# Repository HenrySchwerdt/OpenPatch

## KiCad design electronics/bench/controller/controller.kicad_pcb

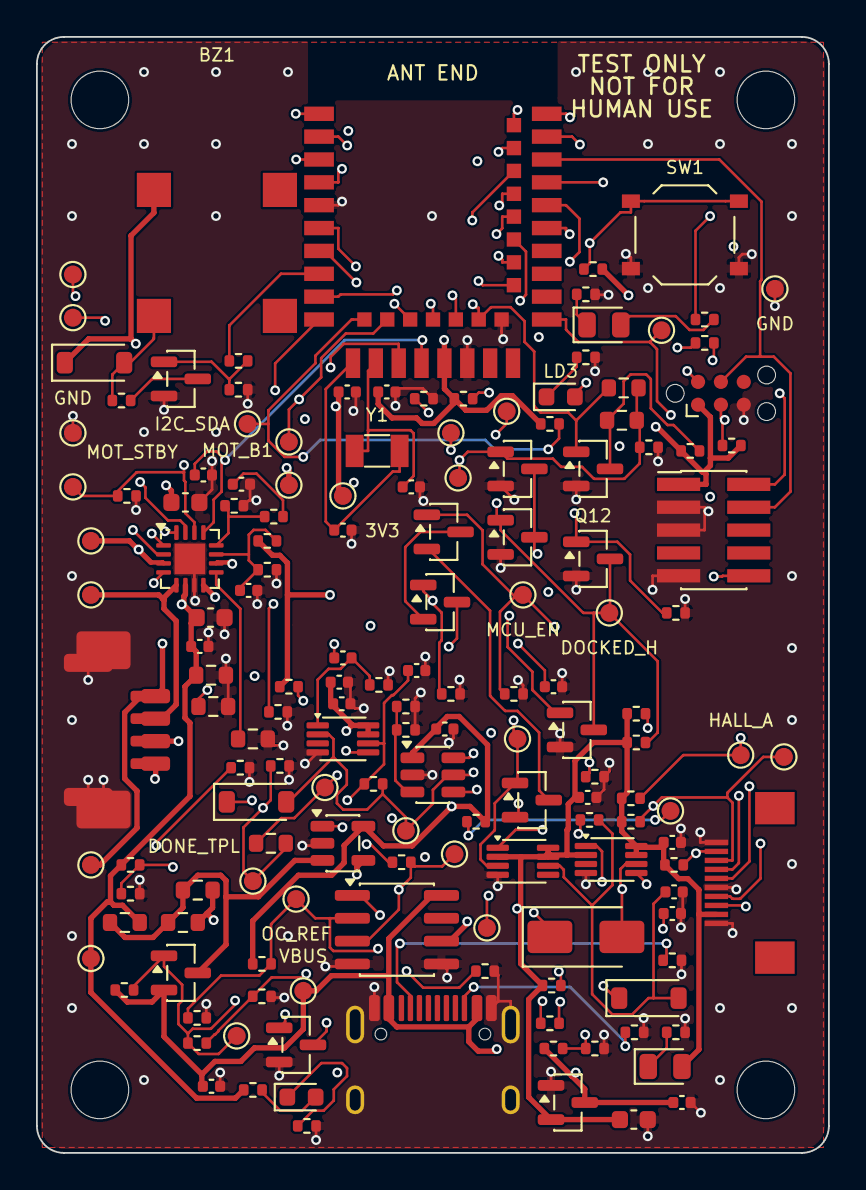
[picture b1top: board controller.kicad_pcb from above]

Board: 4 copper layers, 44.0 x 62.0 mm, 160 parts (0 on the bottom side), 76 nets.

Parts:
BZ1: MLT-8530; Buzzer_MLT-8530_8.5x8.5
C1: 1uF; C_0402_1005Metric
C2: 10uF; C_0603_1608Metric
C4, C20, C24, C25, C26, C27, C28, C29, C33, C34, C35, C36: 100nF; C_0402_1005Metric
C5: 4.7uF; C_0402_1005Metric
C6, C7: 15pF; C_0402_1005Metric
C21, C30, C31, C32: 10nF; C_0402_1005Metric
C22, C23: 10uF 25V; C_0603_1608Metric
D1, D4, D5: 1N4148W; D_SOD-123
D2: SS14; D_SMA
H1, H2, H3, H4: M3; MountingHole_3.2mm_M3
J1: TYPE-C-31-M-12 (power only); USB_C_Receptacle_HRO_TYPE-C-31-M-12
J2: TC2030-IDC-NL; Tag-Connect_TC2030-IDC-NL_2x03_P1.27mm_Vertical
J3: SWD 2x5 1.27 mm; PinHeader_2x05_P1.27mm_Vertical_SMD
J4: FH12-10S-0.5SH(55); Hirose_FH12-10S-0.5SH_1x10-1MP_P0.50mm_Horizontal
J5: PicoBlade 4P (A1251WR-S-4P); Molex_PicoBlade_53261-0471_1x04-1MP_P1.25mm_Horizontal
J6: JST GH SM04B-GHS-TB (DNP alt.); JST_GH_SM04B-GHS-TB_1x04-1MP_P1.25mm_Horizontal
LD1: green 3V3; LED_0805_2012Metric
LD2: green status; LED_0805_2012Metric
LD3: red alarm; LED_0603_1608Metric
LD4: red VMOT on; LED_0603_1608Metric
Q4: AO3401A; SOT-23
Q5, Q6, Q7, Q8, Q9, Q10, Q11, Q12, Q13, Q14: 2N7002; SOT-23
R1, R2, R24: 5.1k; R_0402_1005Metric
R3, R6, R7, R9, R11, R38: 100R; R_0402_1005Metric
R4, R5, R12, R23, R25, R33, R34, R35, R36, R40, R41, R42, R43, R46, R52, R53, R98, R99, R100, R103, R106, R109, R111, R112, R113, R116, R117, R118: 100k; R_0402_1005Metric
R8, R32, R37, R102, R104, R110: 1k; R_0402_1005Metric
R10: 22R; R_0402_1005Metric
R20, R21, R31, R39, R47: 1.0R; R_0603_1608Metric
R22, R30: 47k; R_0402_1005Metric
R26, R44, R107, R108, R114, R115: 10k; R_0402_1005Metric
R45: 22k; R_0402_1005Metric
R50, R51, R105: 4.7k; R_0402_1005Metric
R96, R97, R119: 0R; R_0603_1608Metric
R101: 470R; R_0603_1608Metric
SW1: TS-1187A-B-A-B; SW_Push_1P1T_XKB_TS-1187A
TP1, TP27: GND; TestPoint_Pad_D1.0mm
TP2: 3V3; TestPoint_Pad_D1.0mm
TP3: VBUS; TestPoint_Pad_D1.0mm
TP4: VMOT; TestPoint_Pad_D1.0mm
TP5: PGATE; TestPoint_Pad_D1.0mm
TP6: LATCH_Q; TestPoint_Pad_D1.0mm
TP7: MCU_EN; TestPoint_Pad_D1.0mm
TP8: DOCKED_H; TestPoint_Pad_D1.0mm
TP9: DOCK_N; TestPoint_Pad_D1.0mm
TP10: LATCH_CLR_N; TestPoint_Pad_D1.0mm
TP11: ARM_CLK; TestPoint_Pad_D1.0mm
TP12: WDT_WAKE; TestPoint_Pad_D1.0mm
TP13: WDT_DONE; TestPoint_Pad_D1.0mm
TP14: NRST; TestPoint_Pad_D1.0mm
TP15: MOT_A1; TestPoint_Pad_D1.0mm
TP16: MOT_A2; TestPoint_Pad_D1.0mm
TP17: MOT_B1; TestPoint_Pad_D1.0mm
TP18: MOT_B2; TestPoint_Pad_D1.0mm
TP19: MOT_STCK; TestPoint_Pad_D1.0mm
TP20: MOT_DIR; TestPoint_Pad_D1.0mm
TP21: MOT_STBY; TestPoint_Pad_D1.0mm
TP22: I_SENSE; TestPoint_Pad_D1.0mm
TP23: HALL_A; TestPoint_Pad_D1.0mm
TP24: HALL_B; TestPoint_Pad_D1.0mm
TP28: I2C_SDA; TestPoint_Pad_D1.0mm
TP29: I2C_SCL; TestPoint_Pad_D1.0mm
TP30: DONE_TPL; TestPoint_Pad_D1.0mm
TP31: OC_OK; TestPoint_Pad_D1.0mm
TP32: OC_REF; TestPoint_Pad_D1.0mm
TP41: DIR_REV; TestPoint_Pad_D1.0mm
U1: E73-2G4M08S1CX; Ebyte_E73-2G4M08S1C_13x18
U2: XC6206P332MR-G; SOT-23
U4: STSPIN220; QFN-16-1EP_3x3mm_P0.5mm_EP1.7x1.7mm
U5: TPL5010DDCR; SOT-23-6
U6: SN74AUP1G74DCUR; VSSOP-8_2.3x2mm_P0.5mm
U7: INA180A1IDBVR; SOT-23-5
U8: LM393DR2G; SOIC-8_3.9x4.9mm_P1.27mm
U9: SN74AUP1G74DCUR (OC latch); VSSOP-8_2.3x2mm_P0.5mm
U10: SN74AUP1G74DCUR (DONE qualifier); VSSOP-8_2.3x2mm_P0.5mm
Y1: 32.768kHz 12.5pF; Crystal_SMD_3215-2Pin_3.2x1.5mm

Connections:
3V3: BZ1.1, C2.1, C4.1, C5.1, C25.1, C27.1, C28.1, C33.1, C36.1, D1.1, J2.1, J3.1, J4.2, LD1.2, R4.2, R5.2, R23.1, R26.1, R40.1, R41.1, R46.2, R50.1, R51.1, R52.1, R53.1, R98.1, R107.1, R108.1, R116.1, TP2.1, U1.19, U2.2, U5.1, U6.2, U6.7, U6.8, U7.5, U8.6, U9.2, U9.7, U9.8, U10.7, U10.8
ARM_CLK: R103.1, TP11.1, U1.32, U6.1
BTN_N: R5.1, SW1.1, U1.28
BUZ_PWM: R11.1, U1.8
BZ_D: Q9.3, R10.2
BZ_G: Q9.1, R11.2, R12.1
BZ_N: BZ1.2, D1.2, R10.1
CC1: J1.A5, R1.1
CC2: J1.B5, R2.1
DIR_INV: Q11.3, R97.1, R98.2
DIR_REV: Q10.1, R96.2, R97.2, R99.1, TP41.1, U1.9
DOCKED_H: Q6.1, Q7.3, Q12.3, R40.2, TP8.1, U1.10
DOCK_N: J4.6, Q7.1, R41.2, TP9.1, U1.3
DOCK_TEST: Q12.1, R117.1, U1.2
DONE_PULSE: C31.2, R104.1, U10.1
DONE_TPL: R118.1, R119.2, TP30.1, U5.4, U10.5
GND: C1.2, C2.2, C4.2, C5.2, C6.2, C7.2, C20.2, C21.2, C22.2, C23.2, C24.2, C25.2, C26.2, C27.2, C28.2, C29.2, C30.2, C32.2, C33.2, C34.2, C35.2, C36.2, J1.A1, J1.A12, J1.B1, J1.B12, J1.SH, J2.5, J3.3, J3.5, J3.9, J4.1, J4.5, J4.10, J5.MP, J6.MP, Q6.2, Q7.2, Q9.2, Q10.2, Q11.2, Q12.2, Q14.2, R1.2, R2.2, R3.2, R7.2, R9.2, R12.2, R20.2, R21.2, R22.2, R24.2, R25.2, R34.2, R36.2, R38.2, R42.2, R43.2, R44.2, R45.2, R99.2, R100.2, R101.2, R103.2, R104.2, R109.2, R111.2, R113.2, R114.2, R115.2, R117.2, R118.2, SW1.2, TP1.1, TP27.1, U1.5, U1.21, U1.24, U2.1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
HALL_A: J4.7, R52.2, TP23.1, U1.38
HALL_B: J4.8, R53.2, TP24.1, U1.40
I2C_SCL: J4.4, R51.2, TP29.1, U1.14
I2C_SDA: J4.3, R50.2, TP28.1, U1.12
INA_OUT: R32.1, U7.1
I_SENSE: C26.1, R32.2, TP22.1, U1.7, U8.3
LATCH_CLR_N: C29.1, D2.2, R46.1, TP10.1, U1.34, U6.6
LATCH_Q: Q5.1, R42.1, TP6.1, U1.33, U6.5
LD1_K: LD1.1, R3.1
LD2_K: LD2.1, R7.1
LD3_K: LD3.1, R9.1
LD4_A: LD4.2, R37.2
LD4_K: LD4.1, R38.1
LED_ALM_G: R8.1, U1.42
LED_ALM_R: LD3.2, R8.2
LED_ST_G: R6.1, U1.36
LED_ST_R: LD2.2, R6.2
MCU_EN: D5.1, Q8.1, R43.1, R106.1, TP7.1, U1.35
MOT_A1: J5.4, J6.4, TP15.1, U4.3
MOT_A2: J5.2, J6.2, TP16.1, U4.5
MOT_B1: J5.3, J6.3, TP17.1, U4.10
MOT_B2: J5.1, J6.1, TP18.1, U4.8
MOT_DIR: Q11.1, R96.1, R100.1, TP20.1, U1.22, U4.1
MOT_EN_FAULT: C21.1, R26.2, U1.17, U4.13
MOT_MODE1: R114.1, U4.16
MOT_MODE2: R115.1, U4.15
MOT_REF: C20.1, R23.2, R24.1, U4.11
MOT_STBY: R25.1, TP21.1, U1.1, U4.14
MOT_STCK: TP19.1, U1.20, U4.2
NRST: D2.1, J2.3, J3.10, R4.1, TP14.1, U1.26, U5.6
OC_CLR_N: C35.1, D5.2, R106.2, U9.6
OC_CMP: R107.2, U8.1, U9.1
OC_OK: Q13.1, TP31.1, U1.41, U9.3
OC_REF: R108.2, R109.1, R110.2, TP32.1, U8.2
OC_TEST: Q14.1, R111.1, U1.16
OC_TEST_D: Q14.3, R110.1
PGATE: Q4.1, Q5.3, R30.2, R112.1, TP5.1
PGATE_MON: R112.2, R113.1, U1.43
PG_MID1: Q5.2, Q8.3
PG_MID2: Q6.3, Q10.3, Q13.2
PG_MID2a: Q8.2, Q13.3
POD_ID_N: J4.9, R116.2, U1.6
SNSA: R20.1, U4.4
SNSB: R21.1, U4.9
SWDCLK: J2.4, J3.4, U1.39
SWDIO: J2.2, J3.2, U1.37
TOFF: R22.1, R102.1, U4.12
TOFF_RC: C30.1, R102.2
VBUS: C1.1, C34.1, J1.A4, J1.A9, J1.B4, J1.B9, Q4.2, R30.1, R35.1, TP3.1, U2.3, U8.8
VBUS_SENSE: R35.2, R36.1, U1.15
VMOT: C22.1, C23.1, C24.1, R31.2, R33.1, R37.1, R39.2, R47.2, R101.1, TP4.1, U4.6, U7.4
VMOT_RAW: Q4.3, R31.1, R39.1, R47.1, U7.3
VMOT_SENSE: R33.2, R34.1, U1.18
WAKE_CLR: C32.1, D4.1, R105.1, U10.6
WDT_DELAY: R44.1, R45.1, U5.3
WDT_DONE: C31.1, R119.1, TP13.1, U1.4
WDT_WAKE: D4.2, R105.2, TP12.1, U1.30, U5.5, U10.2
XL1: C6.1, U1.11, Y1.1
XL2: C7.1, U1.13, Y1.2

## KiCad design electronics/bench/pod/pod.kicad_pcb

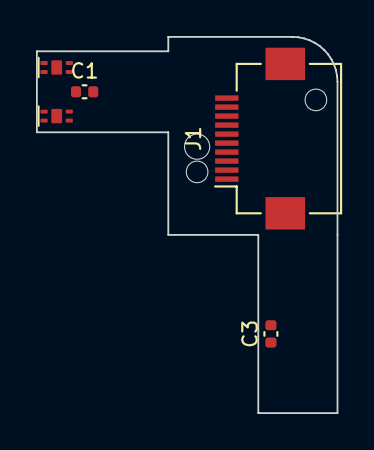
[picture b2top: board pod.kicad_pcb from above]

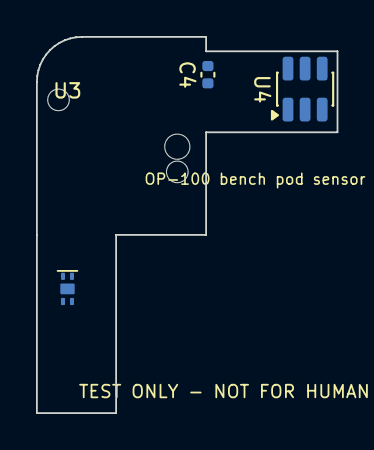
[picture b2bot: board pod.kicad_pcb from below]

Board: 2 copper layers, 16.7 x 20.9 mm, 11 parts (3 on the bottom side), 8 nets, no tracks yet.

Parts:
C1, C3, C4: 100nF; C_0402_1005Metric
H1, H2: NPTH 1.2; NPTH_1.2mm
H3: NPTH 1.4; NPTH_1.4mm
J1: FH12-10S-0.5SH(55); Hirose_FH12-10S-0.5SH_1x10-1MP_P0.50mm_Horizontal
U1, U2, U3: DRV5032FADMR; DRV5032_X2SON-4_DMR0004B
U4: TMAG5273A1QDBVR; SOT-23-6

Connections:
3V3: C1.1, C3.1, C4.1, J1.2, U1.1, U2.1, U3.1, U4.4
DOCK_N: J1.5, U3.4
GND: C1.2, C3.2, C4.2, J1.1, J1.10, J1.MP, U1.2, U1.5, U2.2, U2.5, U3.2, U3.5, U4.2, U4.3
HALL_A: J1.3, U1.4
HALL_B: J1.4, U2.4
I2C_SCL: J1.7, U4.1
I2C_SDA: J1.6, U4.6
TMAG_INT: J1.8, U4.5

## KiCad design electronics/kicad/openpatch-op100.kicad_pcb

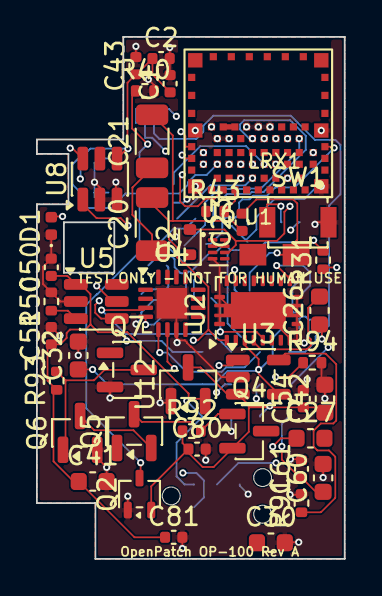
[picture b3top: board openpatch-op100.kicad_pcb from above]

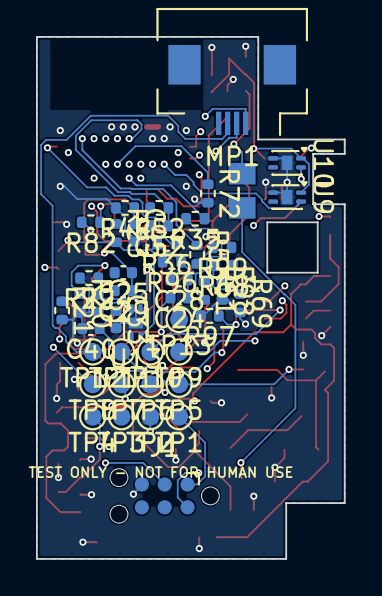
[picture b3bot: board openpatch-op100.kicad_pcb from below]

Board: 4 copper layers, 17.1 x 29.0 mm, 90 parts (46 on the bottom side), 59 nets.

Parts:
BT1: Battery 2-Pad; Contact_Pads_Battery_2x_1.5x1.2
C1, C31, C45, C50, C51, C52, C61, C81: 100nF; C_0402_1005Metric
C2: 4.7uF; C_0402_1005Metric
C20, C21: 100nF C0G 25V; C_1206_3216Metric
C23: 1nF C0G; C_0402_1005Metric
C24, C25: 22nF 25V; C_0402_1005Metric
C26, C27: 470nF 25V; C_0603_1608Metric
C28, C29: 10nF 25V; C_0402_1005Metric
C30, C32: 10uF 25V; C_0603_1608Metric
C33, C40, C43, C54, C80: 1uF; C_0402_1005Metric
C41, C42, C60: 10uF; C_0603_1608Metric
D1: TPD1E10B06DPYR; D_0402_1005Metric
D2: RB521S30; D_SOD-523
J1: TC2030-IDC-NL; Tag-Connect_TC2030-IDC-NL_2x03_P1.27mm_Vertical
LRX1: Qi Rx coil O17.6 ~6-8uH; Contact_Pads_Coil_2x_1.5x1.2
MP1: Motor 4-Pad; Hirose_FH12-4S-0.5SH_derived
Q2: DMG1013UW-7; SOT-323_SC-70
Q4: AO3401A; SOT-23
Q5, Q6, Q7: 2N7002; SOT-23
R20: 3.16k; R_0402_1005Metric
R21: 200R; R_0402_1005Metric
R22: 10k; R_0402_1005Metric
R23, R31, R51, R52, R53, R68, R72, R92, R93, R94, R96: 100k; R_0402_1005Metric
R35, R36: 4.7k; R_0402_1005Metric
R40: 0R; R_0402_1005Metric
R43: 1.5M; R_0402_1005Metric
R44: 1M; R_0402_1005Metric
R50: 6.8k; R_0402_1005Metric
R69: 3.3k; R_0402_1005Metric
R82: 1k; R_0402_1005Metric
R91, R99: 47k; R_0402_1005Metric
R97, R98: 1R0; R_0402_1005Metric
SW1: Button 3.0x2.5x1.2; SW_SPST_B3U-1000P
TP1, TP2, TP3, TP4, TP5, TP6, TP7, TP8, TP9, TP10, TP11, TP12, TP13: TP 0.8mm; TestPoint_Pad_D1.0mm
U1: ISP1807-LR; ISP1807
U2: BQ51003YFPR; Texas_VQFN-RHL-20
U3: MCP73832T-2ACI/OT; SOT-23-5
U4: STSPIN220; QFN-16-1EP_3x3mm_P0.5mm_EP1.7x1.7mm
U5: TPL5010DDCR; SOT-23-6
U6: SN74AUP1G74DQER; X2SON-8_1.4x1mm_P0.35mm
U8: TMAG5273A1QDBVR; SOT-23-6
U9, U10, U13: DRV5032FADMRR; Texas_X2SON-4-1EP_1.1x1.4mm_P0.5mm_EP0.8x0.6mm
U12: XC6206P332MR-G; SOT-23

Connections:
3V3: C1.1, C2.1, C41.1, C43.1, C50.1, C51.1, C81.1, J1.1, R23.2, R31.2, R35.2, R36.2, R51.2, R52.2, R68.1, R93.1, R96.1, TP1.1, U1.26, U5.1, U6.2, U6.7, U6.8, U8.4, U9.1, U10.1, U12.2, U13.1
ARM_CLK: U1.15, U6.1
BTN_N: R82.2, U1.37
BTN_RAW: D1.2, R82.1, SW1.1
CELL_N: BT1.2, R40.1
CHG_PROG: R91.1, U3.5
CHG_STAT: R31.1, U1.29, U3.1
DOCKED_H: Q6.1, Q7.3, R93.2
DOCK_N: Q7.1, R96.2, U1.38, U13.4
GND: C1.2, C2.2, C30.2, C31.2, C32.2, C33.2, C40.2, C41.2, C42.2, C43.2, C45.2, C50.2, C51.2, C52.2, C54.2, C60.2, C61.2, C80.2, C81.2, D1.1, J1.5, Q2.1, Q6.2, Q7.2, R20.2, R21.2, R22.2, R40.2, R44.2, R50.2, R53.2, R69.2, R72.2, R91.2, R94.2, R97.2, R98.2, R99.2, SW1.2, TP2.1, U1.1, U1.7, U1.14, U1.16, U1.18, U1.21, U1.23, U1.24, U1.25, U1.31, U2.1, U2.9, U2.10, U2.11, U2.20, U2.21, U3.2, U4.7, U4.17, U5.2, U6.4, U8.2, U8.3, U9.2, U9.5, U10.2, U10.5, U12.1, U13.2, U13.3, U13.5
HALL_A: TP6.1, U1.49, U9.4
HALL_B: TP7.1, U1.50, U10.4
I2C_SCL: R35.1, TP9.1, U1.39, U8.1
I2C_SDA: R36.1, TP8.1, U1.6, U8.6
LATCH_CLR_N: C52.1, D2.2, R52.1, U1.17, U6.6
MOT_A1: MP1.1, TP10.1, U4.3
MOT_A2: MP1.2, TP11.1, U4.5
MOT_ALLOW: Q5.1, R53.1, U1.9, U6.5
MOT_B1: MP1.3, TP12.1, U4.10
MOT_B2: MP1.4, TP13.1, U4.8
MOT_DIR: U1.11, U4.1
MOT_EN_FAULT: U1.54, U4.13
MOT_MODE1: U1.51, U4.16
MOT_MODE2: U1.52, U4.15
MOT_REF: R68.2, R69.1, U4.11
MOT_STBY: R72.1, U1.53, U4.14
MOT_STCK: U1.45, U4.2
NRST: D2.1, J1.3, R51.1, U1.13, U5.6
PGATE: Q4.1, Q5.3, R92.2
PG_MID: Q5.2, Q6.3
QI_AC1: C20.2, C21.2, C23.1, C24.1, C26.1, C28.1, U2.2
QI_AC2: C23.2, C25.1, C27.1, C29.1, LRX1.2, U2.19
QI_BOOT1: C28.2, U2.3
QI_BOOT2: C29.2, U2.17
QI_CHG_N: R23.1, U1.27, U2.7
QI_CLAMP1: C26.2, U2.5
QI_CLAMP2: C27.2, U2.16
QI_COIL_A: C20.1, C21.1, LRX1.1
QI_COM1: C24.2, U2.6
QI_COM2: C25.2, U2.15
QI_FOD: R21.1, U2.14
QI_ILIM: R20.1, U2.12
QI_TS_CTRL: R22.1, U2.13
RECT: C30.1, C31.1, U2.18
RF_LINK: U1.20, U1.22
SNSA: R97.1, U4.4
SNSB: R98.1, U4.9
SWDCLK: J1.4, U1.30
SWDIO: J1.2, U1.28
TMAG_INT: U1.32, U8.5
TOFF: R99.1, U4.12
VBAT: C42.1, C54.1, C80.1, Q2.2, Q4.2, R43.1, R92.1, TP3.1, U3.3, U12.3
VBAT_RAW: BT1.1, Q2.3
VBAT_SENSE: C45.1, R43.2, R44.1, U1.36
VMOT: C60.1, C61.1, Q4.3, R94.1, TP4.1, U4.6
VQI_5V: C32.1, C33.1, C40.1, TP5.1, U2.4, U3.4
WDT_DELAY: R50.1, U5.3
WDT_DONE: U1.34, U5.4
WDT_WAKE: U1.5, U5.5

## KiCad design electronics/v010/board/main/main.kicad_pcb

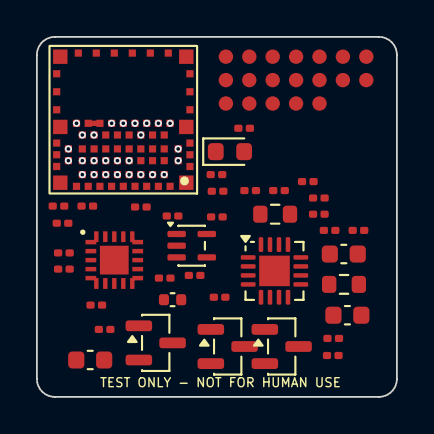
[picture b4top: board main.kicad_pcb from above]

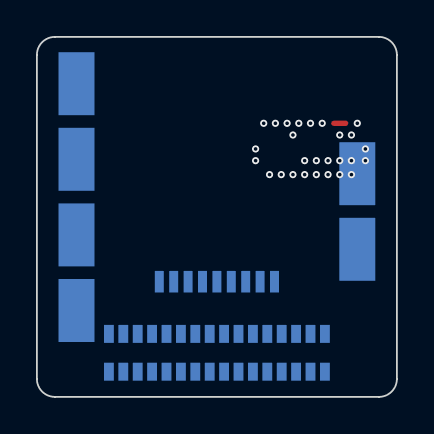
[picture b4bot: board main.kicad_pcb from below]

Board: 6 copper layers, 20.0 x 20.0 mm, 66 parts (8 on the bottom side), 58 nets.

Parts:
C1, C19, C23, C50, C52: 100nF; C_0201_0603Metric
C2: 4.7uF; C_0201_0603Metric
C6: 1uF; C_0402_1005Metric
C7, C22: 10uF; C_0603_1608Metric
C20: 10nF; C_0201_0603Metric
C21: 22uF; C_0603_1608Metric
C51: 1uF; C_0201_0603Metric
J3: SENSOR link pads (9); SENSOR_Pads_9_P0.8
J7: board-to-board pads to POWER (2 x 16); B2B_Pads_2x16_P0.8_M
J10: SWD pad SWDIO; TP_Pad_D0.8
J11: SWD pad SWDCLK; TP_Pad_D0.8
J12: SWD pad NRST; TP_Pad_D0.8
J13: SWD pad GND; TP_Pad_D0.8
J14: SWD pad SUP_SWDIO; TP_Pad_D0.8
J15: SWD pad SUP_SWDCLK; TP_Pad_D0.8
J16: SWD pad SUP_NRST; TP_Pad_D0.8
LD1: red status; LED_0603_1608Metric
MP1, MP2, MP3, MP4: BWCD-L3.5W2.0H1.0 motor pad; Spring_Contact_3.5x2.0
Q7, Q7B: 2N7002; SOT-23
R1, R21, R37, R39, R43, R73, R80, R81: 100k; R_0201_0603Metric
R19, R20: 4.7M; R_0201_0603Metric
R34, R35: 1.0R; R_0603_1608Metric
R36: 47k; R_0201_0603Metric
R38: 5.1k; R_0201_0603Metric
R40: 10k; R_0201_0603Metric
R67, R68: 4.7k; R_0201_0603Metric
R74: 1k; R_0201_0603Metric
R75: 100R; R_0201_0603Metric
SP1, SP2: BWCD-L3.5W2.0H1.0 spring; Spring_Contact_3.5x2.0
TP1: 3V3; TP_Pad_D0.8
TP2: VMOT; TP_Pad_D0.8
TP3: STCK_DRV; TP_Pad_D0.8
TP4: SUP_STCK_EN; TP_Pad_D0.8
TP5: SUP_OK; TP_Pad_D0.8
TP6: SUP_TXD; TP_Pad_D0.8
TP7: SUP_RXD; TP_Pad_D0.8
TP8: ARM_CLK; TP_Pad_D0.8
TP9: MOT_EN_FAULT; TP_Pad_D0.8
TP10: I2C_SDA; TP_Pad_D0.8
TP11: I2C_SCL; TP_Pad_D0.8
TP12: GND; TP_Pad_D0.8
U1: ISP1807-LR (consigned); ISP1807
U2: XC6206P332MR-G; SOT-23
U7: STSPIN220; QFN-16-1EP_3x3mm_P0.5mm_EP1.7x1.7mm
U30: STM32C011F4U6; UFQFPN-20_3x3_P0.5
U31: SN74AUP1G08DCKR; SOT-353_SC-70-5

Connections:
3V3: C1.1, C2.1, C7.1, C50.1, C51.1, C52.1, J3.2, J7.8, R1.1, R19.1, R20.1, R21.1, R40.1, R67.1, R68.1, R73.1, R80.2, TP1.1, U1.26, U2.2, U30.4, U31.5
ARM_CLK: TP8.1, U1.43, U30.7
BTN_N: J7.29, R73.2, U1.37
BUZ_A: J7.30, U1.51
BUZ_B: J7.31, U1.52
CHG_STAT: J7.12, U1.48
DIR_REV: J7.22, U30.9
DOCKED_H: J7.23, Q7.3, Q7B.3, R21.2, U1.44, U30.20
DOCK_N: J3.5, Q7.1, R19.2, U1.3
DOCK_NB: J3.6, Q7B.1, R20.2
DOCK_TEST: J7.24, U1.50
GND: C1.2, C2.2, C6.2, C7.2, C19.2, C20.2, C21.2, C22.2, C23.2, C50.2, C51.2, C52.2, J3.1, J3.8, J3.9, J7.1, J7.4, J7.7, J7.17, J7.32, J13.1, Q7.2, Q7B.2, R34.2, R35.2, R36.2, R38.2, R39.2, R43.2, R75.2, R81.2, SP2.1, TP12.1, U1.1, U1.7, U1.14, U1.16, U1.18, U1.21, U1.23, U1.24, U1.25, U1.31, U2.1, U7.7, U7.15, U7.16, U7.17, U30.5, U30.21, U31.3
I2C_SCL: J3.4, R68.2, TP11.1, U1.39
I2C_SDA: J3.3, R67.2, TP10.1, U1.41
I_SENSE: J7.19, U1.38
LD1_K: LD1.1, R75.1
LED_A: LD1.2, R74.2
LED_ST: R74.1, U1.53
MCU_EN: J7.20, U1.45, U30.1
MOT_A1: MP4.1, U7.3
MOT_A2: MP2.1, U7.5
MOT_B1: MP3.1, U7.10
MOT_B2: MP1.1, U7.8
MOT_DIR: J7.21, U1.33, U7.1
MOT_EN_FAULT: C20.1, R40.2, TP9.1, U1.35, U7.13
MOT_REF: C19.1, R37.2, R38.1, U7.11
MOT_STBY: R37.1, R39.1, U1.32, U7.14
NRST: J12.1, R1.2, U1.13, U30.14
NTC: J7.15, U1.42
OC_OK: J7.26, U1.2, U30.10
OC_TEST: J7.27, U1.49
PGATE_MON: J7.28, U1.4
RF_BRIDGE: U1.20, U1.22
SENSE_EN: J7.16, U1.47
SNSA: R34.1, U7.4
SNSB: R35.1, U7.9
STCK_DRV: TP3.1, U7.2, U31.4
STCK_MCU: R43.1, U1.34, U30.8, U31.1
SUP_NRST: J16.1, R80.1, U30.6
SUP_OK: TP5.1, U1.5, U30.13
SUP_PERMIT: J7.25, U30.12
SUP_RXD: TP7.1, U1.29, U30.17
SUP_STCK_EN: R81.1, TP4.1, U30.11, U31.2
SUP_SWDCLK: J15.1, U30.19
SUP_SWDIO: J14.1, U30.18
SUP_TXD: TP6.1, U1.27, U30.16
SWDCLK: J11.1, U1.30
SWDIO: J10.1, U1.28
TMAG_INT: J3.7, U1.6
TOFF: R36.1, U7.12
USB_DM: J7.11, U1.10
USB_DP: J7.10, U1.8
VBAT: C6.1, J7.2, J7.3, SP1.1, U2.3
VBAT_SENSE: J7.14, U1.36
VBUS_P: J7.9, U1.12
VBUS_SENSE: J7.13, U1.46
VMOT: C21.1, C22.1, C23.1, J7.5, J7.6, TP2.1, U7.6
VMOT_SENSE: J7.18, U1.40

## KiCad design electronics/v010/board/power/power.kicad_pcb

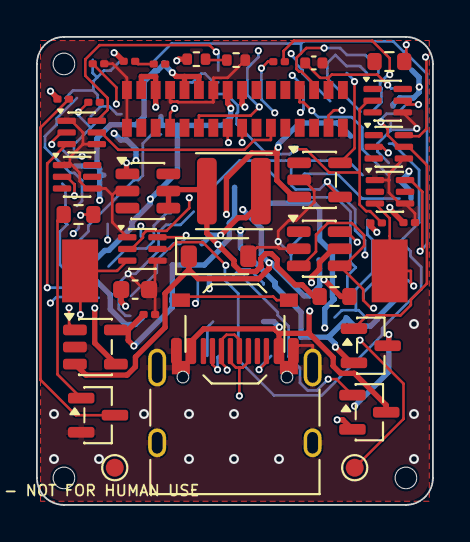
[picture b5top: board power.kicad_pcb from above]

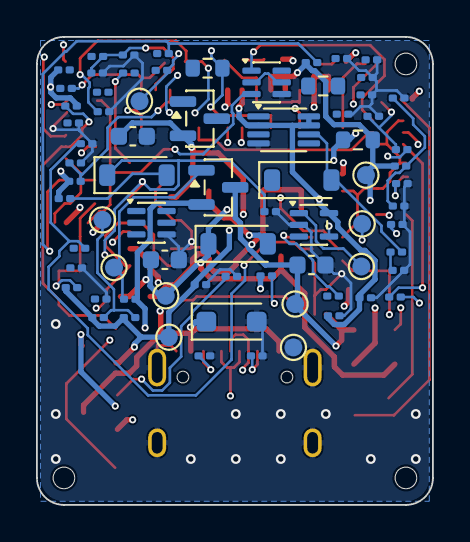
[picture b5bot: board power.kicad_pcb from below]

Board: 4 copper layers, 22.0 x 26.0 mm, 115 parts (74 on the bottom side), 64 nets.

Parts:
C5, C24, C31: 10uF; C_0603_1608Metric
C8, C9: 4.7uF; C_0201_0603Metric
C10, C11, C25, C26, C28, C29, C30, C42, C60: 100nF; C_0201_0603Metric
C27, C32: 10nF; C_0201_0603Metric
CU1: 10uF; C_0603_1608Metric
CU2: 1uF; C_0201_0603Metric
D4: B5819W SL; D_SOD-123
D5: 1N4148W; D_SOD-123
D6: B5819W SL (DNP); D_SOD-123
DU1: SMF5.0A TVS; D_SOD-123F
DZ1: BZT52C6V2 (VMOT overvoltage clamp); D_SOD-123
H1, H2, H3: NPTH 1.2; NPTH_1.2mm
J7P: board-to-board pads to MAIN (2 x 16); B2B_Pads_2x16_P0.8
JU1: USB-C receptacle (proxy: TYPE-C-31-M-12; IPX7 par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; USB_C_Receptacle_HRO_TYPE-C-31-M-12
L1: CKCS4018-4.7uH; L_APV_ANR4018
PZ1: piezo spring pad A; Spring_Contact_3.5x2.0
PZ2: piezo spring pad B; Spring_Contact_3.5x2.0
Q1, Q4, Q15: AO3401A; SOT-23
Q11: 2N7002; SOT-23
QD1: 2N7002DW (Q8 + Q16); SOT-363_SC-70-6
QD2: 2N7002DW (Q13 + Q17); SOT-363_SC-70-6
QD3: 2N7002DW (Q6 + Q20); SOT-363_SC-70-6
QD4: 2N7002DW (Q21 + Q14); SOT-363_SC-70-6
QD5: 2N7002DW (Q10 + Q12); SOT-363_SC-70-6
QD6: 2N7002DW (Q22 + Q2); SOT-363_SC-70-6
QD7: 2N7002DW (QS + QBA); SOT-363_SC-70-6
QD8: 2N7002DW (Q17B + QBB); SOT-363_SC-70-6
QU1: AO3401A (ideal diode / reverse protect); SOT-23
R2: 22R; R_0201_0603Metric
R3: 47k; R_0201_0603Metric
R4: 3.3k; R_0201_0603Metric
R5, R6, R7, R9, R10, R12, R15, R16, R18, R22, R46, R51, R53, R54, R57, R58, R82, R83, R85, R86, R87: 100k; R_0201_0603Metric
R8, R11, R47, R48, R84: 10k; R_0201_0603Metric
R13, R62: 0R; R_0603_1608Metric
R14, R63: 0R DNP; R_0603_1608Metric
R24, R25: 100R; R_0201_0603Metric
R44: 0.22R; R_0603_1608Metric
R45: 0R DNP (boost bypass); R_0603_1608Metric
R49, R50: 1M; R_0201_0603Metric
R52: 1k; R_0201_0603Metric
R55: 220k; R_0402_1005Metric
R56: 30k; R_0402_1005Metric
RBA: 1k; R_0201_0603Metric
RBB: 1k; R_0201_0603Metric
RDA: 100k; R_0201_0603Metric
RDB: 100k; R_0201_0603Metric
RGA: 100R; R_0201_0603Metric
RGB: 100R; R_0201_0603Metric
RT1: NTC 10k NCP15XH103F03RC; C_0402_1005Metric
RU1, RU2: 5.1k; R_0201_0603Metric
RU3: 100k; R_0201_0603Metric
SW1: TS-1187A-B-A-B; SW_Push_1P1T_XKB_TS-1187A
TP1: GND; TestPoint_Pad_D1.0mm
TP2: VBAT; TestPoint_Pad_D1.0mm
TP3: VMOT; TestPoint_Pad_D1.0mm
TP4: VMOT_RAW; TestPoint_Pad_D1.0mm
TP5: VMOT_PRE; TestPoint_Pad_D1.0mm
TP6: PGATE; TestPoint_Pad_D1.0mm
TP7: PGATE2; TestPoint_Pad_D1.0mm
TP8: INA_OUT; TestPoint_Pad_D1.0mm
TP9: OC_CMP; TestPoint_Pad_D1.0mm
TP10: CH_TOP; TestPoint_Pad_D1.0mm
TP11: PG_MID2; TestPoint_Pad_D1.0mm
TP12: VCHG; TestPoint_Pad_D1.0mm
U3: MCP73832T-2ACI/OT; SOT-23-5
U8: MT3608 (DNP); SOT-23-6
U9: INA180A1IDBVR; SOT-23-5
U11: TLV7011DCKR; SOT-353_SC-70-5
U12: SN74AUP1G74DCUR; VSSOP-8_2.3x2mm_P0.5mm
UU1: USBLC6-2SC6; SOT-23-6

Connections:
3V3: C28.1, C29.1, J7P.8, R12.1, R49.1, R87.1, U11.5, U12.2, U12.7, U12.8
BLD: QD2.3, QD8.6, R24.2, R25.2
BST_FB: R55.2, R56.1, U8.3
BST_SW: D6.2, L1.2, U8.1
BTN_N: C42.1, J7P.29, SW1.1
BUZ_A: J7P.30, RGA.1
BUZ_B: J7P.31, RGB.1
BZ_GA: QD7.5, RDA.1, RGA.2
BZ_GB: QD8.5, RDB.1, RGB.2
CC1: JU1.A5, RU1.1
CC2: JU1.B5, RU2.1
CHG_P2: R3.2, R4.1
CHG_PROG: R3.1, U3.5
CHG_R: D4.2, R2.2
CHG_STAT: J7P.12, U3.1
CH_TOP: QD1.6, R11.2, TP10.1
DIR_INV: Q11.3, R12.2, R14.1, R62.1
DIR_REV: J7P.22, QD6.2, R13.2, R14.2, R15.1
DOCKED_H: J7P.23, QD3.2, QD3.5, QD5.3
DOCK_NOT: QD3.3, QD5.2, R87.2
DOCK_TEST: J7P.24, QD5.5, R22.1
FWD: QD4.2, R62.2, R63.2
GND: C5.2, C8.2, C9.2, C10.2, C24.2, C25.2, C26.2, C27.2, C28.2, C29.2, C30.2, C31.2, C32.2, C42.2, CU1.2, CU2.2, DU1.2, DZ1.2, J7P.1, J7P.4, J7P.7, J7P.17, J7P.32, JU1.A1, JU1.A12, JU1.B1, JU1.B12, JU1.SH, Q11.2, QD1.4, QD2.4, QD3.4, QD4.1, QD4.4, QD5.4, QD6.1, QD6.4, QD7.1, QD7.4, QD8.1, QD8.4, R4.2, R7.2, R15.2, R16.2, R18.2, R22.2, R46.2, R51.2, R53.2, R56.2, R58.2, R82.2, R86.2, RDA.2, RDB.2, RT1.2, RU1.2, RU2.2, RU3.2, SW1.2, TP1.1, U3.2, U8.2, U9.2, U11.2, U12.4, UU1.2
INA_OUT: R46.1, R47.1, R48.1, TP8.1, U9.1
I_SENSE: C26.1, J7P.19, R47.2
MCU_EN: D5.1, J7P.20, QD1.2, R18.1, R54.1
MOT_DIR: J7P.21, Q11.1, R13.1, R16.1, R63.1
NTC: J7P.15, R8.2, RT1.1
OC_CLR_N: C30.1, D5.2, R54.2, U12.6
OC_CMP: TP9.1, U11.1, U12.1
OC_IN: C27.1, R48.2, U11.3
OC_OK: J7P.26, QD2.2, U12.3
OC_REF: R49.2, R50.1, R52.2, U11.4
OC_REF2: R50.2, R51.1
OC_TEST: J7P.27, QD4.5, R53.1
OC_TEST_D: QD4.3, R52.1
PGATE: C11.1, Q4.1, QD1.5, QD2.5, R9.2, R10.2, R11.1, TP6.1
PGATE2: C60.1, Q15.1, QD8.2, R83.2, R84.1, TP7.1
PGATE_MON: J7P.28, QD1.3
PG_MID2: QD1.1, QD2.6, TP11.1
PG_MID2A: QD2.1, QD3.6, QD5.6
PZ_A: PZ1.1, QD7.3, RBA.2
PZ_B: PZ2.1, QD8.3, RBB.2
QS_D: QD7.6, R84.2
SENSE_EN: J7P.16, QD6.5, R8.1
SP_G: Q1.1, QD6.3, R5.2
SUP_PERMIT: J7P.25, QD7.2, R82.1
USB_DM: J7P.11, JU1.A7, JU1.B7, UU1.3, UU1.4
USB_DP: J7P.10, JU1.A6, JU1.B6, UU1.1, UU1.6
VBAT: C5.1, C9.1, C11.2, J7P.2, J7P.3, Q1.2, Q4.2, R5.1, R9.1, R10.1, RBA.1, RBB.1, TP2.1, U3.3
VBAT_SENSE: C10.1, J7P.14, R6.2, R7.1
VBAT_SW: Q1.3, R6.1
VBUS_G: QU1.1, RU3.1
VBUS_P: CU1.1, J7P.9, QU1.2, R2.1, R85.1
VBUS_R: CU2.1, DU1.1, JU1.A4, JU1.A9, JU1.B4, JU1.B9, QU1.3, UU1.5
VBUS_SENSE: J7P.13, R85.2, R86.1
VCHG: C8.1, D4.1, TP12.1, U3.4
VMOT: J7P.5, J7P.6, R24.1, R25.1, R44.2, R57.1, TP3.1, U9.4
VMOT_A: C60.2, Q4.3, Q15.2, R83.1
VMOT_PRE: C31.1, D6.1, DZ1.1, R44.1, R45.2, R55.1, TP5.1, U9.3
VMOT_RAW: C24.1, C25.1, L1.1, Q15.3, R45.1, TP4.1, U8.4, U8.5, U9.5
VMOT_SENSE: C32.1, J7P.18, R57.2, R58.1
XA: QD3.1, QD4.6
XB: QD5.1, QD6.6

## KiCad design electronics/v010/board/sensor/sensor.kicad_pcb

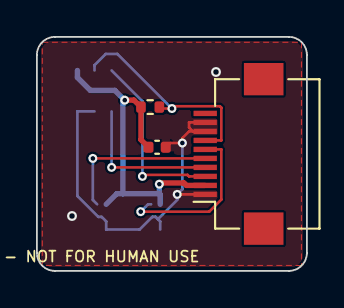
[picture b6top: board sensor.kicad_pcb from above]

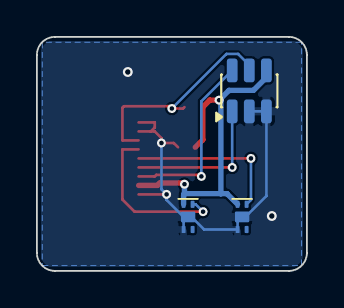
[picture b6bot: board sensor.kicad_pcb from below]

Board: 2 copper layers, 15.0 x 13.0 mm, 6 parts (3 on the bottom side), 7 nets.

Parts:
C41: 100nF; C_0402_1005Metric
J3S: FH12-10S-0.5SH(55); Hirose_FH12-10S-0.5SH_1x10-1MP_P0.50mm_Horizontal
R69: 100k; R_0402_1005Metric
U4A, U4B: DRV5032AJDMRR; DRV5032_X2SON-4_DMR0004B
U10T: TMAG5273A1QDBVR; SOT-23-6

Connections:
3V3: C41.1, J3S.2, R69.1, U4A.1, U4B.1, U10T.4
DOCK_N: J3S.5, U4A.4
DOCK_NB: J3S.6, U4B.4
GND: C41.2, J3S.1, J3S.8, J3S.9, U4A.2, U4A.5, U4B.2, U4B.5, U10T.2, U10T.3
I2C_SCL: J3S.4, U10T.1
I2C_SDA: J3S.3, U10T.6
TMAG_INT: J3S.7, R69.2, U10T.5

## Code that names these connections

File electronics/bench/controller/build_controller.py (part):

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          note="Torex pinout 1 GND, 2 OUT, 3 IN (differs from clones)")
    C("C1", "1uF", "VBUS", "GND", 37.5, 50.6)
    C6("C2", "10uF", "3V3", "GND", 38.5, 53.2)
    b.add("LD1", "green 3V3", ("LED_SMD", "LED_0805_2012Metric"), 40.2, 49.0, 90, pins={"1": "LD1_K", "2": "3V3"}, lcsc="C2297", mpn="KT-0805G")
    R("R3", "100R", "LD1_K", "GND", 40.2, 46.8, 90)

    # ------------------------------------------------------------------ SWD / reset / button / LEDs
    b.add("J2", "TC2030-IDC-NL", ("Connector", "Tag-Connect_TC2030-IDC-NL_2x03_P1.27mm_Vertical"), 37.0, 21.0, 0,
          pins={"1": "3V3", "2": "SWDIO", "3": "NRST", "4": "SWDCLK", "5": "GND"}, bom=False)
    b.add("J3", "SWD 2x5 1.27 mm", ("Connector_PinHeader_1.27mm", "PinHeader_2x05_P1.27mm_Vertical_SMD"), 39.5, 31.0, 0,
          pins={"1": "3V3", "2": "SWDIO", "3": "GND", "4": "SWDCLK", "5": "GND", "9": "GND", "10": "NRST"},
          lcsc="C41376037", mpn="PZ1.27-2x5P TP", bom=False, note="DNP (extended part, saves a setup fee): footprint for a 2x5 1.27 mm SWD header; use the Tag-Connect pads J2")
    R("R4", "100k", "NRST", "3V3", 33.0, 19.6)
    b.add("SW1", "TS-1187A-B-A-B", ("Button_Switch_SMD", "SW_Push_1P1T_XKB_TS-1187A"), 38.0, 8.0, 0, pins={"1": "BTN_N", "2": "GND"},
          lcsc="C318884", mpn="TS-1187A-B-A-B")
    R("R5", "100k", "BTN_N", "3V3", 33.2, 12.4)
    b.add("LD2", "green status", ("LED_SMD", "LED_0805_2012Metric"), 31.5, 14.8, 0, pins={"1": "LD2_K", "2": "LED_ST_R"}, lcsc="C2297", mpn="KT-0805G")
    R("R6", "100R", "LED_ST_G", "LED_ST_R", 34.2, 14.8)
    R("R7", "100R", "LD2_K", "GND", 29.4, 14.8)
    b.add("LD3", "red alarm", ("LED_SMD", "LED_0603_1608Metric"), 31.5, 17.0, 0, pins={"1": "LD3_K", "2": "LED_ALM_R"}, lcsc="C2286", mpn="KT-0603R")
    R("R8", "1k", "LED_ALM_G", "LED_ALM_R", 34.2, 17.0)
    R("R9", "100R", "LD3_K", "GND", 29.4, 17.0)

    # ------------------------------------------------------------------ buzzer
    b.add("BZ1", "MLT-8530", ("Bench", "Buzzer_MLT-8530_8.5x8.5"), 9.5, 11.0, 0, pins={"1": "3V3", "2": "BZ_N"}, lcsc="C94599", mpn="MLT-8530", bom=False, note="DNP in Rev A (extended part); alarms via LEDs / BLE")
    b.add("D1", "1N4148W", ("Diode_SMD", "D_SOD-123"), 5.0, 17.5, 0, pins={"1": "3V3", "2": "BZ_N"}, lcsc="C81598", mpn="1N4148W")
    R("R10", "22R", "BZ_N", "BZ_D", 5.0, 19.3)
    b.add("Q9", "2N7002", SOT23, 8.0, 19.0, 0, pins={"1": "BZ_G", "2": "GND", "3": "BZ_D"}, lcsc="C8545", mpn="2N7002")
    R("R11", "100R", "BUZ_PWM", "BZ_G", 11.2, 18.0)
    R("R12", "100k", "BZ_G", "GND", 11.2, 19.6)

    # ------------------------------------------------------------------ STSPIN220 + current sense
    b.add("U4", "STSPIN220", ("Package_DFN_QFN", "QFN-16-1EP_3x3mm_P0.5mm_EP1.7x1.7mm"), 8.5, 29.0, 0,
          pins={"1": "MOT_DIR", "2": "MOT_STCK", "3": "MOT_A1", "4": "SNSA", "5": "MOT_A2", "6": "VMOT", "7": "GND", "8": "MOT_B2",
                "9": "SNSB", "10": "MOT_B1", "11": "MOT_REF", "12": "TOFF", "13": "MOT_EN_FAULT", "14": "MOT_STBY", "15": "MOT_MODE2",
                "16": "MOT_MODE1", "17": "GND"}, lcsc="C2150516", mpn="STSPIN220")
    b.add("R20", "1.0R", R0603, 5.0, 33.0, 0, pins={"1": "SNSA", "2": "GND"}, lcsc="C174300", mpn="RS-03L1R00FT")
    b.add("R21", "1.0R", R0603, 12.0, 33.0, 0, pins={"1": "SNSB", "2": "GND"}, lcsc="C174300", mpn="RS-03L1R00FT")
    R("R22", "47k", "TOFF", "GND", 11.8, 26.2)
    R("R102", "1k", "TOFF", "TOFF_RC", 11.8, 24.6)
    C("C30", "10nF", "TOFF_RC", "GND", 13.6, 24.6)
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    C("C24", "100nF", "VMOT", "GND", 11.0, 36.0)

    # ------------------------------------------------------------------ motor supply switch (interlock) + shunt
    b.add("Q4", "AO3401A", SOT23, 8.0, 46.0, 0, pins={"1": "PGATE", "2": "VBUS", "3": "VMOT_RAW"}, lcsc="C15127", mpn="AO3401A")
    R("R30", "47k", "VBUS", "PGATE", 11.5, 46.0)
    b.add("R31", "1.0R", R0603, 8.0, 41.5, 0, pins={"1": "VMOT_RAW", "2": "VMOT"}, lcsc="C174300", mpn="RS-03L1R00FT")
    b.add("R39", "1.0R", R0603, 8.0, 43.4, 0, pins={"1": "VMOT_RAW", "2": "VMOT"}, lcsc="C174300", mpn="RS-03L1R00FT", note="parallel with R31/R47: 0.333 ohm shunt")
    b.add("R47", "1.0R", R0603, 8.0, 45.3, 0, pins={"1": "VMOT_RAW", "2": "VMOT"}, lcsc="C174300", mpn="RS-03L1R00FT", note="parallel with R31/R39: 0.333 ohm shunt")
    b.add("U7", "INA180A1IDBVR", SOT235, 17.0, 40.0, 0, pins={"1": "INA_OUT", "2": "GND", "3": "VMOT_RAW", "4": "VMOT", "5": "3V3"},
          lcsc="C122228", mpn="INA180A1IDBVR", note="Pinout A: 1 OUT, 2 GND, 3 IN+, 4 IN-, 5 VS")
    C("C25", "100nF", "3V3", "GND", 17.0, 37.6)
    R("R32", "1k", "INA_OUT", "I_SENSE", 20.0, 40.0)
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    R("R34", "100k", "VMOT_SENSE", "GND", 4.0, 41.6)
    R("R35", "100k", "VBUS", "VBUS_SENSE", 27.0, 51.0)
    R("R36", "100k", "VBUS_SENSE", "GND", 27.0, 52.6)
    b.add("LD4", "red VMOT on", ("LED_SMD", "LED_0603_1608Metric"), 15.0, 52.0, 0, pins={"1": "LD4_K", "2": "LD4_A"}, lcsc="C2286", mpn="KT-0603R")
    R("R37", "1k", "VMOT", "LD4_A", 15.0, 50.4)
    R("R38", "100R", "LD4_K", "GND", 15.0, 53.6)
    b.add("R101", "470R", R0603, 13.0, 44.0, 0, pins={"1": "VMOT", "2": "GND"}, lcsc="C23179", mpn="0603WAF4700T5E",
          note="VMOT bleeder: VMOT falls below 1.8 V within about 10 ms after the supply switch opens")

    # INTERLOCK (see ../INTERLOCK.md):  VMOT on = LATCH_Q AND MCU_EN AND (DOCKED OR DIR_REV)
    # P-FET Q4 closes only when PGATE is pulled low through Q5 (watchdog latch) - Q8 (MCU enable) - [Q6 docked || Q10 DIR reverse] - GND
    b.add("Q5", "2N7002", SOT23, 24.0, 28.0, 0, pins={"1": "LATCH_Q", "2": "PG_MID1", "3": "PGATE"}, lcsc="C8545", mpn="2N7002")
    b.add("Q8", "2N7002", SOT23, 27.5, 28.0, 0, pins={"1": "MCU_EN", "2": "PG_MID2a", "3": "PG_MID1"}, lcsc="C8545", mpn="2N7002")
    b.add("Q13", "2N7002", SOT23, 27.5, 34.0, 0, pins={"1": "OC_OK", "2": "PG_MID2", "3": "PG_MID2a"}, lcsc="C8545", mpn="2N7002",
          note="4th series leg: hardware over-current latch (U9) must be OK")
    b.add("Q6", "2N7002", SOT23, 31.0, 28.0, 0, pins={"1": "DOCKED_H", "2": "GND", "3": "PG_MID2"}, lcsc="C8545", mpn="2N7002")
    # refill/draw: motion in the REVERSE direction (plunger retracts, nothing is delivered) is allowed undocked.
    # DIR_REV = MOT_DIR (R96 fitted: DIR high = reverse, the restrictive default because a stuck-low / unpowered DIR = forward = blocked)
    # or its inverse (R97 fitted instead: DIR low = reverse). The polarity must be confirmed on the first motor (INTERLOCK.md, test T5).
    b.add("Q10", "2N7002", SOT23, 30.0, 24.0, 0, pins={"1": "DIR_REV", "2": "GND", "3": "PG_MID2"}, lcsc="C8545", mpn="2N7002",
          note="parallel to Q6: pull-down path is closed if DOCKED OR DIR_REV")
    b.add("Q11", "2N7002", SOT23, 33.0, 24.0, 0, pins={"1": "MOT_DIR", "2": "GND", "3": "DIR_INV"}, lcsc="C8545", mpn="2N7002", note="inverter for the optional inverted DIR_REV polarity")
    R("R98", "100k", "3V3", "DIR_INV", 33.0, 26.0)
    R("R99", "100k", "DIR_REV", "GND", 28.0, 24.0)
    R("R100", "100k", "MOT_DIR", "GND", 26.0, 24.0)
    b.add("R96", "0R", R0603, 35.0, 24.0, 0, pins={"1": "MOT_DIR", "2": "DIR_REV"}, lcsc="C21189", mpn="0603WAF0000T5E", note="DIR_REV = DIR (fitted by default: DIR high = reverse/retract; firmware DIR_FORWARD_HIGH must be false; verify on the motor)")
    b.add("R97", "0R", R0603, 37.0, 24.0, 0, pins={"1": "DIR_INV", "2": "DIR_REV"}, bom=False, note="DNP: fit instead of R96 if DIR low retracts the plunger")
    b.add("Q7", "2N7002", SOT23, 31.0, 33.0, 0, pins={"1": "DOCK_N", "2": "GND", "3": "DOCKED_H"}, lcsc="C8545", mpn="2N7002")
    R("R40", "100k", "3V3", "DOCKED_H", 34.2, 33.0)
    R("R41", "100k", "3V3", "DOCK_N", 34.2, 31.2)
    R("R42", "100k", "LATCH_Q", "GND", 24.0, 31.0)
    R("R43", "100k", "MCU_EN", "GND", 27.5, 31.0)

    # ------------------------------------------------------------------ watchdog + latch
    b.add("U5", "TPL5010DDCR", SOT236, 22.0, 35.0, 0, pins={"1": "3V3", "2": "GND", "3": "WDT_DELAY", "4": "DONE_TPL", "5": "WDT_WAKE", "6": "NRST"},
          lcsc="C473912", mpn="TPL5010DDCR")
    R("R44", "10k", "WDT_DELAY", "GND", 19.0, 33.0)
    R("R45", "22k", "WDT_DELAY", "GND", 19.0, 34.6)
    C("C27", "100nF", "3V3", "GND", 22.0, 32.6)
    b.add("U6", "SN74AUP1G74DCUR", ("Package_SO", "VSSOP-8_2.3x2mm_P0.5mm"), 28.0, 38.5, 0,
          pins={"1": "ARM_CLK", "2": "3V3", "3": None, "4": "GND", "5": "LATCH_Q", "6": "LATCH_CLR_N", "7": "3V3", "8": "3V3"},
          lcsc="C140267", mpn="SN74AUP1G74DCUR")
    C("C28", "100nF", "3V3", "GND", 31.0, 38.0)
    R("R46", "100k", "LATCH_CLR_N", "3V3", 28.0, 41.5)
    R("R103", "100k", "ARM_CLK", "GND", 31.0, 35.4)
    C("C29", "100nF", "LATCH_CLR_N", "GND", 30.0, 41.5)
    b.add("D2", "SS14", ("Diode_SMD", "D_SMA"), 36.5, 38.5, 90, pins={"1": "NRST", "2": "LATCH_CLR_N"}, lcsc="C2480", mpn="SS14")


    # ------------------------------------------------------------------ discrete safety additions (no MCU-programmable element in the cut path)
    # force-"undocked" for the power-on self test: can only pull DOCKED_H LOW, never force it on
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
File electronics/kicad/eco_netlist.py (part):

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ECO = [
    "U2 BQ51003YFP (DSBGA-28, 0.4 mm pitch) -> BQ51013BRHLR (VQFN-20 4.5x3.5, same pin functions): no via-in-pad, assemblable on JLC.",
    "U2 AD pin -> GND and AD_EN left floating (SKiDL had AD_EN=GND, AD=NC: datasheet says AD tied to PGND if unused, AD-EN is a push-pull output, float).",
    "U3 BQ25120AYFP (DSBGA-25, 0.4 mm) removed -> MCP73832T-2ACI/OT (SOT-23-5) charger, PROG=47k (~21 mA) + U12 XC6206P332MR 3.3 V LDO (VIN=VBAT). Loses I2C charger/VBAT monitor/LS-LDO/MR. PER_EN pin unused; BQ_INT net renamed CHG_STAT (STAT open drain).",
    "U7 TPS22916 (DSBGA-4) removed -> discrete high-side switch Q4 AO3401A + Q5/Q6 2N7002 series gate pull-down: VMOT on only if MOT_ALLOW AND DOCKED (new interlock). R92 gate pull-up (fail-safe off).",
    "NEW dock hall U13 DRV5032FA + inverter Q7 + R93/R96 (fail-safe: no signal = not docked) ; DOCK_N routed to ISP1807 pad 38 (P0.03).",
    "U4 STSPIN220: added SENSEA/SENSEB sense resistors (1.0 ohm, R97/R98) and TOFF resistor R99=47k to GND (all required by datasheet, missing in SKiDL netlist); REF divider R68/R69 set for VREF=0.105 V (Ipk ~ 105 mA, verify against motor).",
    "U8 TMAG5273 pin 3 'GND (TEST)' must be tied to GND (SKiDL had it NC).",
    "R50 TPL5010 DELAY resistor 6.8k -> 2 s watchdog interval (MCUboot); DS Table 3: 6.788k.",
    "Removed: 9x9 piezo BZ1, Q1, R80, R81 (bench sample, no buzzer); DW01A/FS8205A PCM option (U11,Q3,R41,R42,C44); BQ25120A TS/MR/CD pulls (R30,R32,R33,R34); L4.",
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LEAN_REMOVE = {"R62", "R63", "R64", "R65", "R66", "R67", "R70", "R71", "C62", "C70", "C71", "C72"}
LEAN_MERGE = {"MOT_STCK_DRV": "MOT_STCK", "MOT_DIR_DRV": "MOT_DIR", "MOT_MODE1_DRV": "MOT_MODE1",
              "MOT_MODE2_DRV": "MOT_MODE2", "MOT_STBY_DRV": "MOT_STBY", "MOT_EN_FAULT_DRV": "MOT_EN_FAULT"}
ECO.append("LEAN (needed to fit the 17.1x29 mm outline): removed 10k series resistors R62-R67 on STSPIN220 logic lines (MCU pins drive the driver directly; MOT_STBY keeps pulldown R72), removed VMOT_SENSE divider R70/R71/C62 (VMOT rail check lost) and hall decoupling C70-C72 (C43 + C81 remain).")


def build(lean: bool = True) -> dict:
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
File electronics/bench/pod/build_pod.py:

#!/usr/bin/env python3
"""Bench pod sensor board from mechanical/out/bench/OP-100.layout.json (KiCad python3).

Board frame of the layout: bx right, by up, viewed from the TOP (lid side, F.Cu). KiCad frame used here: x = bx, y = H - by.
Deviations from the layout (all documented in ../ORDER.md and the final report):
  * DRV5032 X2SON land pattern is 2.1 mm wide when rotated: HALL_A/B centres moved +0.2 mm in x (copper-to-edge >= 0.2 mm).
  * FFC connector is the real Hirose FH12-10S footprint (8.1 x 5.6 mm body + solder tabs +-5.05 mm), not 7.4 x 4.0 mm.
  * TMAG5273 is NOT fitted (10-pin FFC has no pins for I2C).
  * Rev A bench decision: the motor is NOT on this board (factory lead plugs into the controller): no motor contacts, no motor lines on the FFC.
"""
import json
import os
import sys

HERE = os.path.dirname(os.path.abspath(__file__))
sys.path.insert(0, os.path.join(HERE, "..", "tools"))
import pcbnew
import benchlib as bl
from benchlib import Board, write_project, legalize, box_in_poly

LAY = json.load(open(os.path.join(HERE, "..", "..", "..", "mechanical", "out", "bench", "OP-100.layout.json")))
PCB = os.path.join(HERE, "pod.kicad_pcb")
bl.TRACK, bl.CLEAR, bl.VIA_D, bl.VIA_H = 0.2, 0.15, 0.5, 0.3

OUTL = [tuple(p) for p in LAY["board"]["outline_polygon_board_mm"]]
BX = LAY["board"]["bbox_mm"]
H = BX[1]
Y = lambda by: H - by                       # layout (y up) -> KiCad (y down)
poly = [(x, Y(y)) for x, y in OUTL]

R0402, C0402 = ("Resistor_SMD", "R_0402_1005Metric"), ("Capacitor_SMD", "C_0402_1005Metric")
X2SON = ("Bench", "DRV5032_X2SON-4_DMR0004B")
POWER = ("3V3",)


def build(with_tmag=True):
    b = Board("pod", BX[0], H, layers=2, outline=poly)
    b.poly_outline(poly)
    hs = {h["id"]: h for h in LAY["hall_sensors"]}
    
    # ---- dock hall (bottom, in the tower recess), TMAG5273 (bottom, mandatory), optional DRV5032 quadrature pair (top)
    cx, cy = hs["HALL_DOCK"]["center_board_mm"]
    b.add("U3", "DRV5032FADMR", X2SON, cx, Y(cy), 0, side="B", pins={"1": "3V3", "2": "GND", "4": "DOCK_N", "5": "GND"}, lcsc="C2152496", mpn="DRV5032FADMRR",
          note="threshold 3.9 mT switches about 4 mm before full latch; AJ variant C2152498 (9.5 mT) is footprint compatible but not in JLC stock")
    cx, cy = hs["HALL_3D"]["center_board_mm"]
    b.add("U4", "TMAG5273A1QDBVR", ("Package_TO_SOT_SMD", "SOT-23-6"), cx, Y(cy), 90, side="B",
          pins={"1": "I2C_SCL", "2": "GND", "3": "GND", "4": "3V3", "5": "TMAG_INT", "6": "I2C_SDA"}, lcsc="C3716049", mpn="TMAG5273A1QDBVR", note="mandatory angle sensor")
    for ref, hid, out in (("U1", "HALL_A", "HALL_A"), ("U2", "HALL_B", "HALL_B")):
        cx, cy = hs[hid]["center_board_mm"]
        b.add(ref, "DRV5032FADMR", X2SON, cx + 0.2, Y(cy), 90, side="F", pins={"1": "3V3", "2": "GND", "4": out, "5": "GND"}, lcsc="C2152496", mpn="DRV5032FADMRR",
              note="optional coarse quadrature channel (delete from BOM/CPL to leave unpopulated)")
    # ---- decoupling
    for ref, side, x, y in (("C1", "F", 2.65, Y(17.85)), ("C3", "F", 12.8, Y(4.4)), ("C4", "B", 3.6, Y(19.8))):
        b.add(ref, "100nF", C0402, x, y, 0 if ref == "C1" else 90, side=side, pins={"1": "3V3", "2": "GND"}, lcsc="C1525", mpn="CL05B104KO5NNNC")
    # ---- FFC connector, top side, cable exit +X (rot 90), pin 1 toward -by
    ffc = {"1": "GND", "2": "3V3", "3": "HALL_A", "4": "HALL_B", "5": "DOCK_N", "6": "I2C_SDA", "7": "I2C_SCL", "8": "TMAG_INT", "10": "GND", "MP": "GND"}
    b.add("J1", "FH12-10S-0.5SH(55)", ("Connector_FFC-FPC", "Hirose_FH12-10S-0.5SH_1x10-1MP_P0.50mm_Horizontal"), float(os.environ.get("J1X", 12.4)),
          Y(float(os.environ.get("J1Y", 15.25))), 90, pins=ffc, lcsc="C506791", mpn="FH12-10S-0.5SH(55)")
    # ---- holes
    for i, h in enumerate(LAY["mounting"]["locating_pins"]):
        b.add(f"H{i+1}", "NPTH 1.2", ("Bench", "NPTH_1.2mm"), h["center_board_mm"][0], Y(h["center_board_mm"][1]), bom=False, hide_ref=True)
    s = LAY["mounting"]["screw"]
    b.add("H3", "NPTH 1.4", ("Bench", "NPTH_1.4mm"), s["center_board_mm"][0], Y(s["center_board_mm"][1]), bom=False, hide_ref=True)
    b.text("TEST ONLY - NOT FOR HUMAN USE", 5.0, Y(1.2), 0.7, layer=pcbnew.B_SilkS, mirror=True, thick=0.1)
    b.text("OP-100 bench pod sensor rev A", 3.2, Y(13.0), 0.6, layer=pcbnew.B_SilkS, mirror=True, thick=0.09)

    # keep-outs from the layout (components): circles -> square boxes (per side handled by legalize on both sides: conservative)
    forb = []
    for c in LAY["keepout_circles"]:
        cx, cy = c["center_board_mm"]; r = c["d_mm"] / 2
        forb.append([cx - r, Y(cy) - r, cx + r, Y(cy) + r])
    fixed = ["U1", "U2", "U3", "U4", "J1"]
    inside = lambda bx: box_in_poly(bx, poly, 0.15)
    print("legalize moved", legalize(b, fixed, inside=inside, forbid=forb, step=0.2, rmax=8.0))
    b.rules(power_nets=POWER, power_w=0.25, track=0.2)
    bds = b.b.GetDesignSettings(); bds.m_CopperEdgeClearance = bl.MM(0.2); bds.m_MinClearance = bl.MM(0.15)
    b.save(PCB)
    json.dump(b.parts, open(os.path.join(HERE, "parts.json"), "w"), indent=1)
    write_project(os.path.join(HERE, "pod.kicad_pro"), POWER, 0.25, 0.2, edge=0.2, clear=0.15)
    print("pod board written", len(b.parts), "parts")


if __name__ == "__main__":
    build(with_tmag=True)
